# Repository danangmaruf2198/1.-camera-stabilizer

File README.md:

# 1.-camera-stabilizer
this project is about arduino controlling DSLR camera stabilizer spesifically for videography.
-THANKS FOR DOWNLOADING-

Motorized Camera Slider using 3d print mechanical and control stepper motor using arduino with oled display. 
Can using manual mode, auto mode automatically run can adjust range and speed also run multiply. Speed control mode is run auto control speed using potentiometer.
for more detail, visit this video tutorial https://www.youtube.com/watch?v=Y6bwRcumjGc

Gerber File download= https://goo.gl/JGV3JK
3D Print File = https://bit.ly/2X4Sq9Z

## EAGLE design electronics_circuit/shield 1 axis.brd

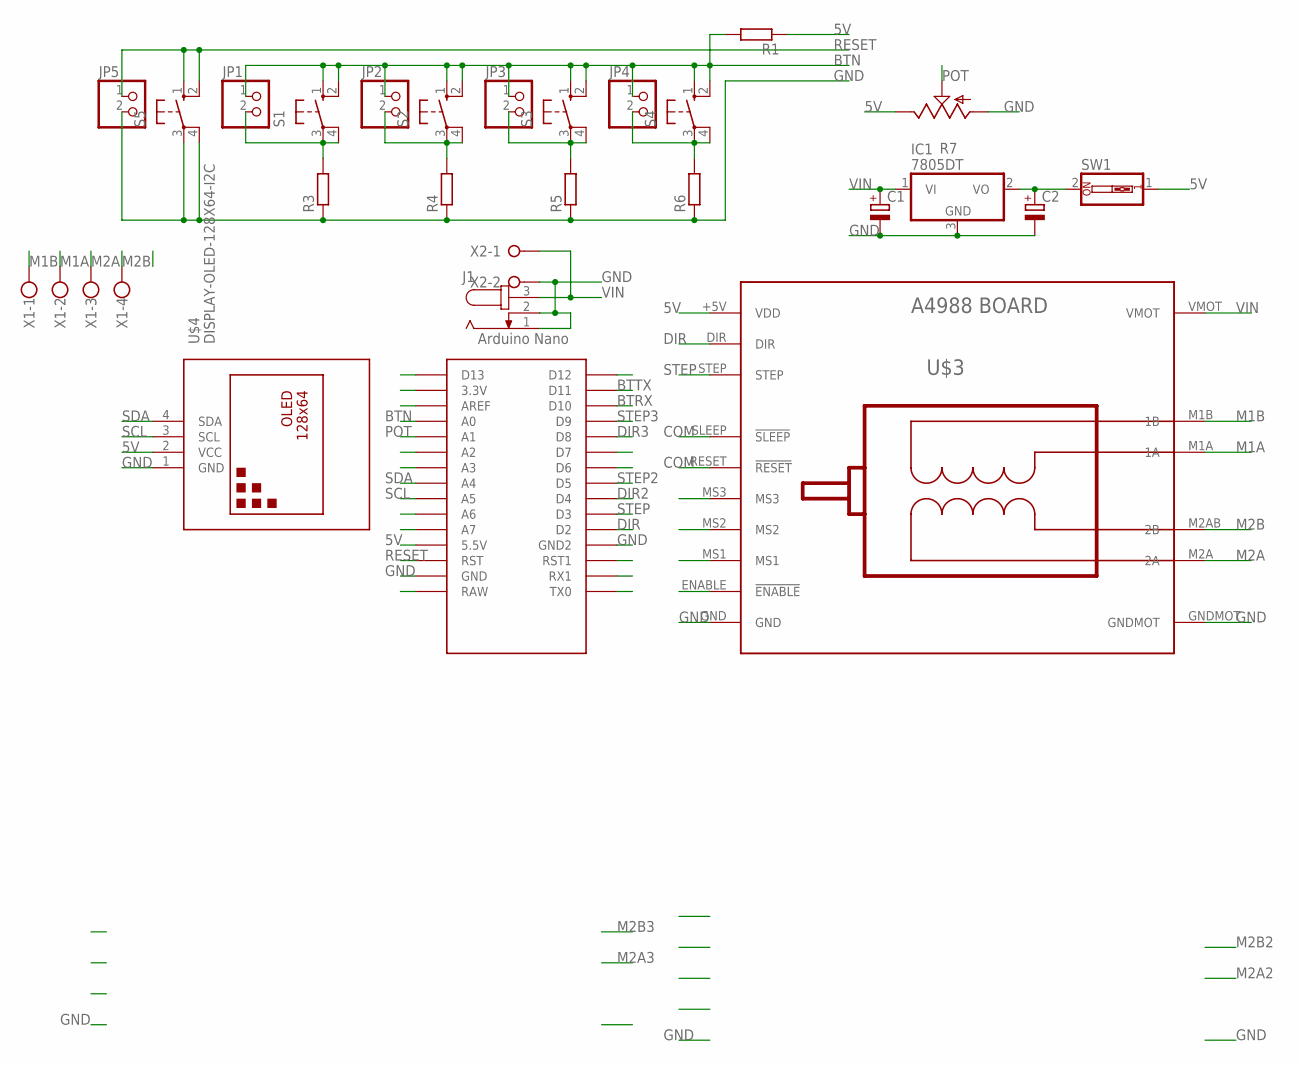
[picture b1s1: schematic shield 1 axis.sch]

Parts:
C1, C2: CPOL-EUE2.5-7; E2,5-7
IC1: 7805DT; TO252
J1: JACK-PLUG1; SPC4078
JP1, JP2, JP3, JP4, JP5: PINHD-1X2; 1X02
R1, R3, R4, R5, R6: R-EU_R1206; R1206
R7: TRIM_US-S63S; S63S
S1, S2, S3, S4: 40-XX; B3F-40XX
S5: 10-XX; B3F-10XX
SW1: SW_DIP-1; EDG-01
U$1: NANO
U$3: BOARD_A4988
U$4: DISPLAY-OLED-128X64-I2C
X1: W237-4
X2: W237-02P; W237-132

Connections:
5V: R1.1, R7.E, SW1.1, U$1.5V (5.5V), U$3.+5V (VDD), U$4.2 (VCC)
BTN: JP1.1, JP2.1, JP3.1, JP4.1, R1.2, S1.1 (S), S1.2 (S1), S2.1 (S), S2.2 (S1), S3.1 (S), S3.2 (S1), S4.1 (S), S4.2 (S1), U$1.A0
BTN1: JP4.2, R6.2, S4.3, S4.4 (P1)
BTN2: JP3.2, R5.2, S3.3, S3.4 (P1)
BTN3: JP2.2, R4.2, S2.3, S2.4 (P1)
BTN4: JP1.2, R3.2, S1.3, S1.4 (P1)
BTRX: U$1.D10
BTTX: U$1.D11
COM: U$3.RESET (!RESET), U$3.SLEEP (!SLEEP)
DIR: U$1.D2, U$3.DIR
DIR2: U$1.D4
DIR3: U$1.D8
GND: C1.-, C2.-, IC1.3 (GND), J1.1, J1.2, JP5.2, R3.1, R4.1, R5.1, R6.1, R7.A, S5.3, S5.4 (P1), U$1.GND, U$1.GND1 (GND2), U$3.GND, U$3.GNDMOT, U$4.1 (GND), X2.2
M1A: U$3.M1A (1A), X1.2
M1B: U$3.M1B (1B), X1.1
M2A: U$3.M2A (2A), X1.3
M2B: U$3.M2AB (2B), X1.4
unnamed: C2.+, IC1.2 (VO), SW1.2
POT: R7.S, U$1.A1
RESET: JP5.1, S5.1 (S), S5.2 (S1), U$1.RST
SCL: U$1.A5, U$4.3 (SCL)
SDA: U$1.A4, U$4.4 (SDA)
STEP: U$1.D3, U$3.STEP
STEP2: U$1.D5
STEP3: U$1.D9
VIN: C1.+, IC1.1 (VI), J1.3, U$3.VMOT, X2.1

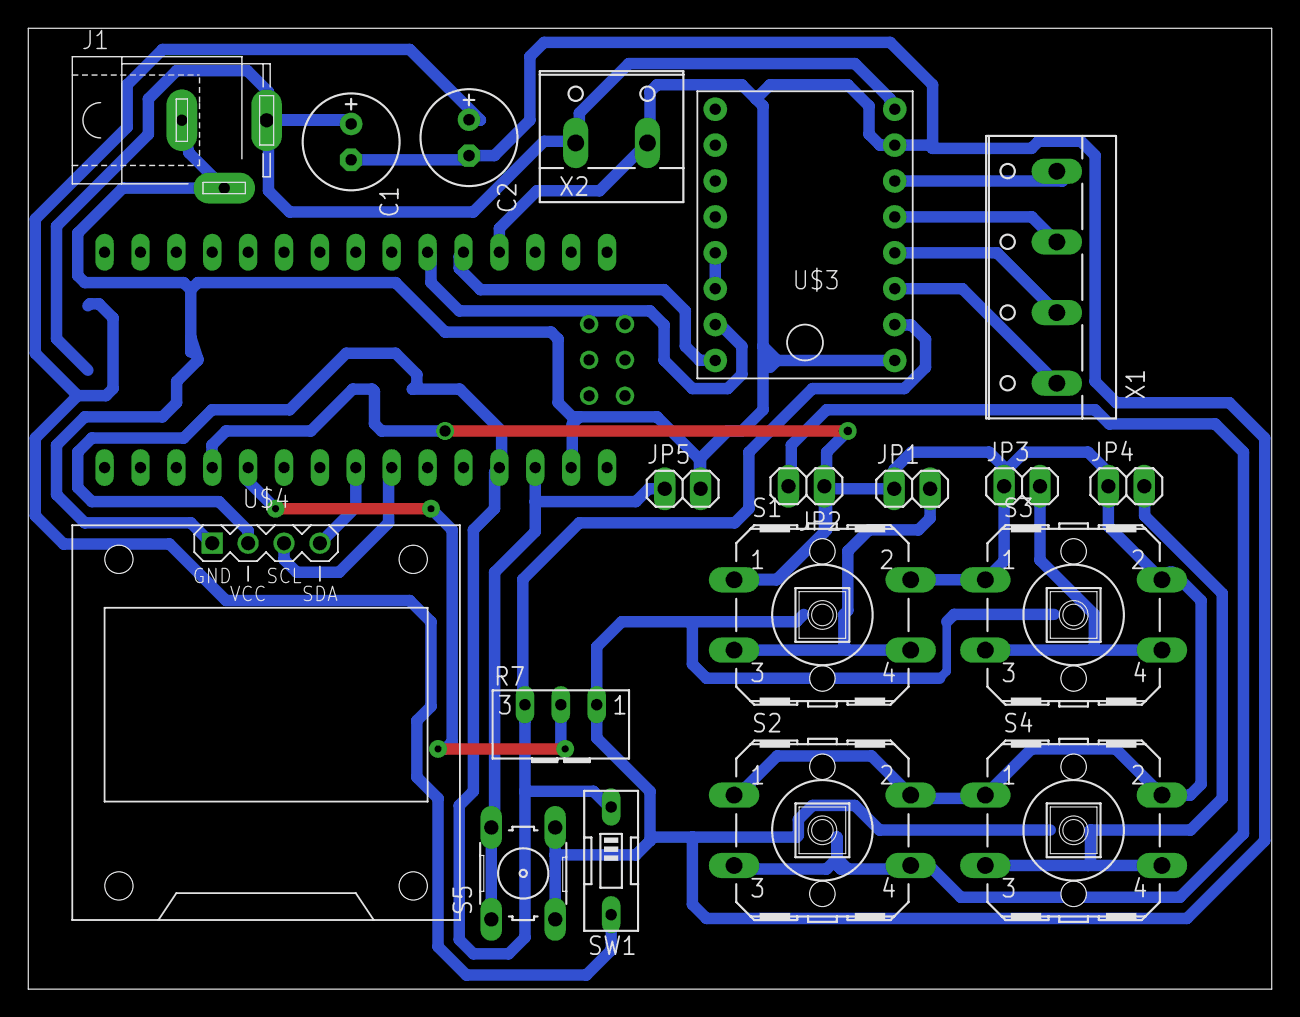
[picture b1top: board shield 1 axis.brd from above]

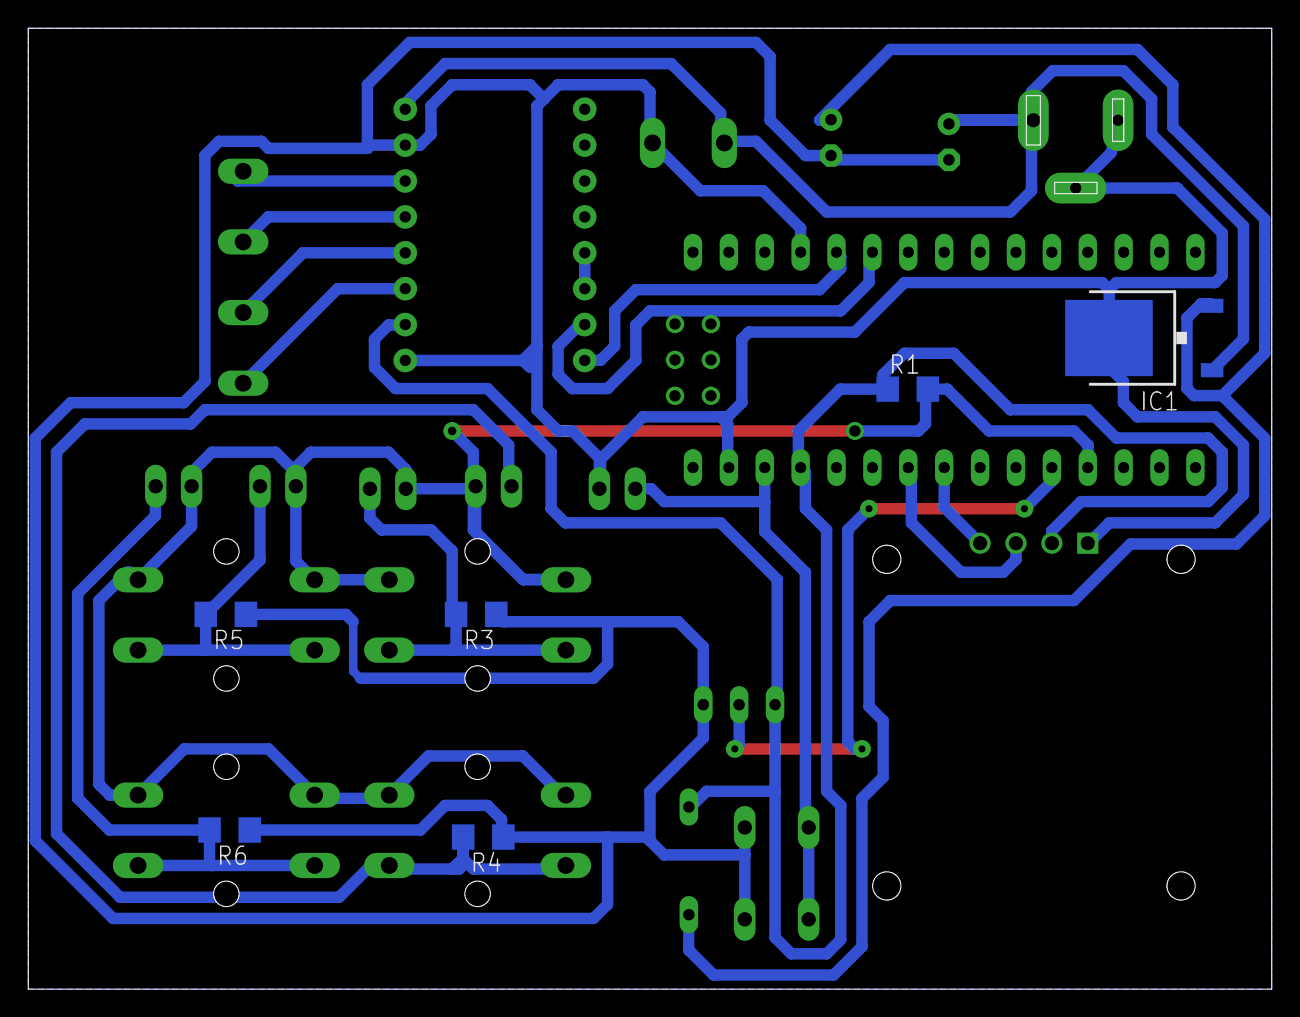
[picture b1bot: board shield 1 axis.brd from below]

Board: 2 copper layers, 88.0 x 68.0 mm, 26 parts (6 on the bottom side), 20 nets.

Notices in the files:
parts and their libraries:
diy-modules: Released under the Creative Commons Attribution 4.0 International License: http://creativecommons.org/licenses/by/4.0
